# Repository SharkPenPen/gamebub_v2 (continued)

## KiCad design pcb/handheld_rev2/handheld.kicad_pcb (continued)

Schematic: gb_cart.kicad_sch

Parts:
C1901, C1902, C1903, C1904, C1905, C1906, C1907, C1908, C1909, C1910, C1911, C1912, C1913: 100n; C_0402_1005Metric; LCSC C1525
J1901: Cartridge_Slot; GameBoy_Cartridge_AGS_1x32-1MP_P1.50mm_Socket_Horizontal
R1901, R1902, R1905: 49R9; R_0402_1005Metric; LCSC C25120
R1903: 100K; R_0402_1005Metric; LCSC C25741
R1904: 27K; R_0603_1608Metric; LCSC C22967
U1901, U1903: 74LVC1T45; SOT-363_SC-70-6; LCSC C168855
U1902, U1904: 74LVCH16T245; TSSOP-48_6.1x12.5mm_P0.5mm; LCSC C352975

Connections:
+3V3_FPGA: C1903.2, C1904.2, C1906.2, C1909.2, C1912.2, C1913.2, R1903.1, U1901.1 (VCCA), U1902.31 (VCCA), U1902.42 (VCCA), U1903.1 (VCCA), U1904.31 (VCCA), U1904.42 (VCCA); also elsewhere on the board
/Game Boy Interfaces/Game Boy Cartridge/Cart_A16: J1901.22 (A16/D0), U1902.12 (1B8)
/Game Boy Interfaces/Game Boy Cartridge/Cart_A17: J1901.23 (A17/D1), U1902.11 (1B7)
/Game Boy Interfaces/Game Boy Cartridge/Cart_A18: J1901.24 (A18/D2), U1902.9 (1B6)
/Game Boy Interfaces/Game Boy Cartridge/Cart_A19: J1901.25 (A19/D3), U1902.8 (1B5)
/Game Boy Interfaces/Game Boy Cartridge/Cart_A20: J1901.26 (A20/D4), U1902.6 (1B4)
/Game Boy Interfaces/Game Boy Cartridge/Cart_A21: J1901.27 (A21/D5), U1902.5 (1B3)
/Game Boy Interfaces/Game Boy Cartridge/Cart_A22: J1901.28 (A22/D6), U1902.3 (1B2)
/Game Boy Interfaces/Game Boy Cartridge/Cart_A23: J1901.29 (A23/D7), U1902.2 (1B1)
/Game Boy Interfaces/Game Boy Cartridge/Cart_AD0: J1901.6 (AD0/A0), U1904.12 (1B8)
/Game Boy Interfaces/Game Boy Cartridge/Cart_AD1: J1901.7 (AD1/A1), U1904.11 (1B7)
/Game Boy Interfaces/Game Boy Cartridge/Cart_AD2: J1901.8 (AD2/A2), U1904.9 (1B6)
/Game Boy Interfaces/Game Boy Cartridge/Cart_AD3: J1901.9 (AD3/A3), U1904.8 (1B5)
/Game Boy Interfaces/Game Boy Cartridge/Cart_AD4: J1901.10 (AD4/A4), U1904.6 (1B4)
/Game Boy Interfaces/Game Boy Cartridge/Cart_AD5: J1901.11 (AD5/A5), U1904.5 (1B3)
/Game Boy Interfaces/Game Boy Cartridge/Cart_AD6: J1901.12 (AD6/A6), U1904.3 (1B2)
/Game Boy Interfaces/Game Boy Cartridge/Cart_AD7: J1901.13 (AD7/A7), U1904.2 (1B1)
/Game Boy Interfaces/Game Boy Cartridge/Cart_AD8: J1901.14 (AD8/A8), U1902.23 (2B8)
/Game Boy Interfaces/Game Boy Cartridge/Cart_AD9: J1901.15 (AD9/A9), U1902.22 (2B7)
/Game Boy Interfaces/Game Boy Cartridge/Cart_AD10: J1901.16 (AD10/A10), U1902.20 (2B6)
/Game Boy Interfaces/Game Boy Cartridge/Cart_AD11: J1901.17 (AD11/A11), U1902.19 (2B5)
/Game Boy Interfaces/Game Boy Cartridge/Cart_AD12: J1901.18 (AD12/A12), U1902.17 (2B4)
/Game Boy Interfaces/Game Boy Cartridge/Cart_AD13: J1901.19 (AD13/A13), U1902.16 (2B3)
/Game Boy Interfaces/Game Boy Cartridge/Cart_AD14: J1901.20 (AD14/A14), U1902.14 (2B2)
/Game Boy Interfaces/Game Boy Cartridge/Cart_AD15: J1901.21 (AD15/A15), U1902.13 (2B1)
/Game Boy Interfaces/Game Boy Cartridge/Cart_PHI: J1901.2 (PHI), U1904.17 (2B4)
/Game Boy Interfaces/Game Boy Cartridge/Cart_VIN: J1901.31 (~REQ/VIN), R1903.2, U1903.4 (B)
/Game Boy Interfaces/Game Boy Cartridge/Cart_~CS1: R1902.1, U1904.13 (2B1)
/Game Boy Interfaces/Game Boy Cartridge/Cart_~CS1_d: J1901.5 (~CS1/~CS), R1902.2
/Game Boy Interfaces/Game Boy Cartridge/Cart_~CS2: R1905.2, U1901.4 (B)
/Game Boy Interfaces/Game Boy Cartridge/Cart_~CS2_d: J1901.30 (~CS2/~RES), R1904.2, R1905.1
/Game Boy Interfaces/Game Boy Cartridge/Cart_~RD: J1901.4 (~RD), U1904.14 (2B2)
/Game Boy Interfaces/Game Boy Cartridge/Cart_~WR: R1901.2, U1904.16 (2B3)
/Game Boy Interfaces/Game Boy Cartridge/Cart_~WR_d: J1901.3 (~WR), R1901.1
GB_Cart_A16: U1902.37 (1A8); also elsewhere on the board
GB_Cart_A17: U1902.38 (1A7); also elsewhere on the board
GB_Cart_A18: U1902.40 (1A6); also elsewhere on the board
GB_Cart_A19: U1902.41 (1A5); also elsewhere on the board
GB_Cart_A20: U1902.43 (1A4); also elsewhere on the board
GB_Cart_A21: U1902.44 (1A3); also elsewhere on the board
GB_Cart_A22: U1902.46 (1A2); also elsewhere on the board
GB_Cart_A23: U1902.47 (1A1); also elsewhere on the board
GB_Cart_AD0: U1904.37 (1A8); also elsewhere on the board
GB_Cart_AD1: U1904.38 (1A7); also elsewhere on the board
GB_Cart_AD2: U1904.40 (1A6); also elsewhere on the board
GB_Cart_AD3: U1904.41 (1A5); also elsewhere on the board
GB_Cart_AD4: U1904.43 (1A4); also elsewhere on the board
GB_Cart_AD5: U1904.44 (1A3); also elsewhere on the board
GB_Cart_AD6: U1904.46 (1A2); also elsewhere on the board
GB_Cart_AD7: U1904.47 (1A1); also elsewhere on the board
GB_Cart_AD8: U1902.26 (2A8); also elsewhere on the board
GB_Cart_AD9: U1902.27 (2A7); also elsewhere on the board
GB_Cart_AD10: U1902.29 (2A6); also elsewhere on the board
GB_Cart_AD11: U1902.30 (2A5); also elsewhere on the board
GB_Cart_AD12: U1902.32 (2A4); also elsewhere on the board
GB_Cart_AD13: U1902.33 (2A3); also elsewhere on the board
GB_Cart_AD14: U1902.35 (2A2); also elsewhere on the board
GB_Cart_AD15: U1902.36 (2A1); also elsewhere on the board
GB_Cart_PHI: U1904.32 (2A4); also elsewhere on the board
GB_Cart_VIN: U1903.3 (A); also elsewhere on the board
GB_Cart_~CS1: U1904.36 (2A1); also elsewhere on the board
GB_Cart_~CS2: U1901.3 (A); also elsewhere on the board
GB_Cart_~OE: U1902.25 (2~OE), U1902.48 (1~OE), U1904.25 (2~OE), U1904.48 (1~OE); also elsewhere on the board
GB_Cart_~RD: U1904.35 (2A2); also elsewhere on the board
GB_Cart_~WR: U1904.33 (2A3); also elsewhere on the board
GB_Dir_Cart0: U1902.1 (1DIR); also elsewhere on the board
GB_Dir_Cart1: U1902.24 (2DIR); also elsewhere on the board
GB_Dir_Cart2: U1904.1 (1DIR); also elsewhere on the board
GB_Dir_Cart3: U1904.24 (2DIR); also elsewhere on the board
GB_Dir_VIN: U1903.5 (DIR); also elsewhere on the board
GB_Dir_~CS2: U1901.5 (DIR); also elsewhere on the board
GND: C1901.1, C1902.1, C1903.1, C1904.1, C1905.1, C1906.1, C1907.1, C1908.1, C1909.1, C1910.1, C1911.1, C1912.1, C1913.1, J1901.32 (GND), J1901.MP, U1901.2 (GND), U1902.4 (GND), U1902.10 (GND), U1902.15 (GND), U1902.21 (GND), U1902.28 (GND), U1902.34 (GND), U1902.39 (GND), U1902.45 (GND), U1903.2 (GND), U1904.4 (GND), U1904.10 (GND), U1904.15 (GND), U1904.19 (2B5), U1904.20 (2B6), U1904.21 (GND), U1904.22 (2B7), U1904.23 (2B8), U1904.26 (2A8), U1904.27 (2A7), U1904.28 (GND), U1904.29 (2A6), U1904.30 (2A5), U1904.34 (GND), U1904.39 (GND), U1904.45 (GND); also elsewhere on the board
VGB: C1901.2, C1902.2, C1905.2, C1907.2, C1908.2, C1910.2, C1911.2, J1901.1 (VDD), R1904.1, U1901.6 (VCCB), U1902.7 (VCCB), U1902.18 (VCCB), U1903.6 (VCCB), U1904.7 (VCCB), U1904.18 (VCCB); also elsewhere on the board

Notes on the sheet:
AGS uses 18K for CS2 pull-up
AGS uses 47Ω for WR/CS1 resistor
AGS uses 15Ω for CS2 limiter

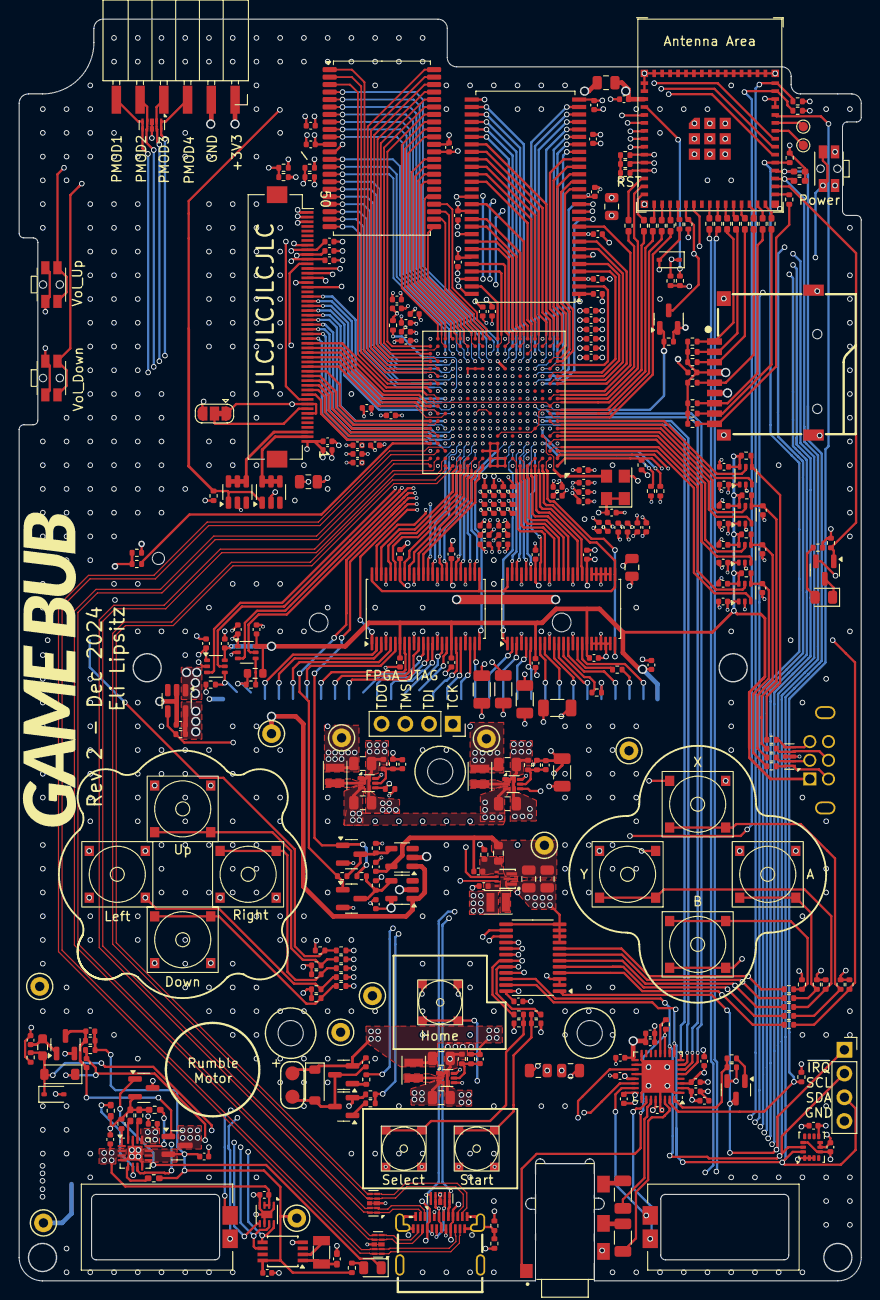
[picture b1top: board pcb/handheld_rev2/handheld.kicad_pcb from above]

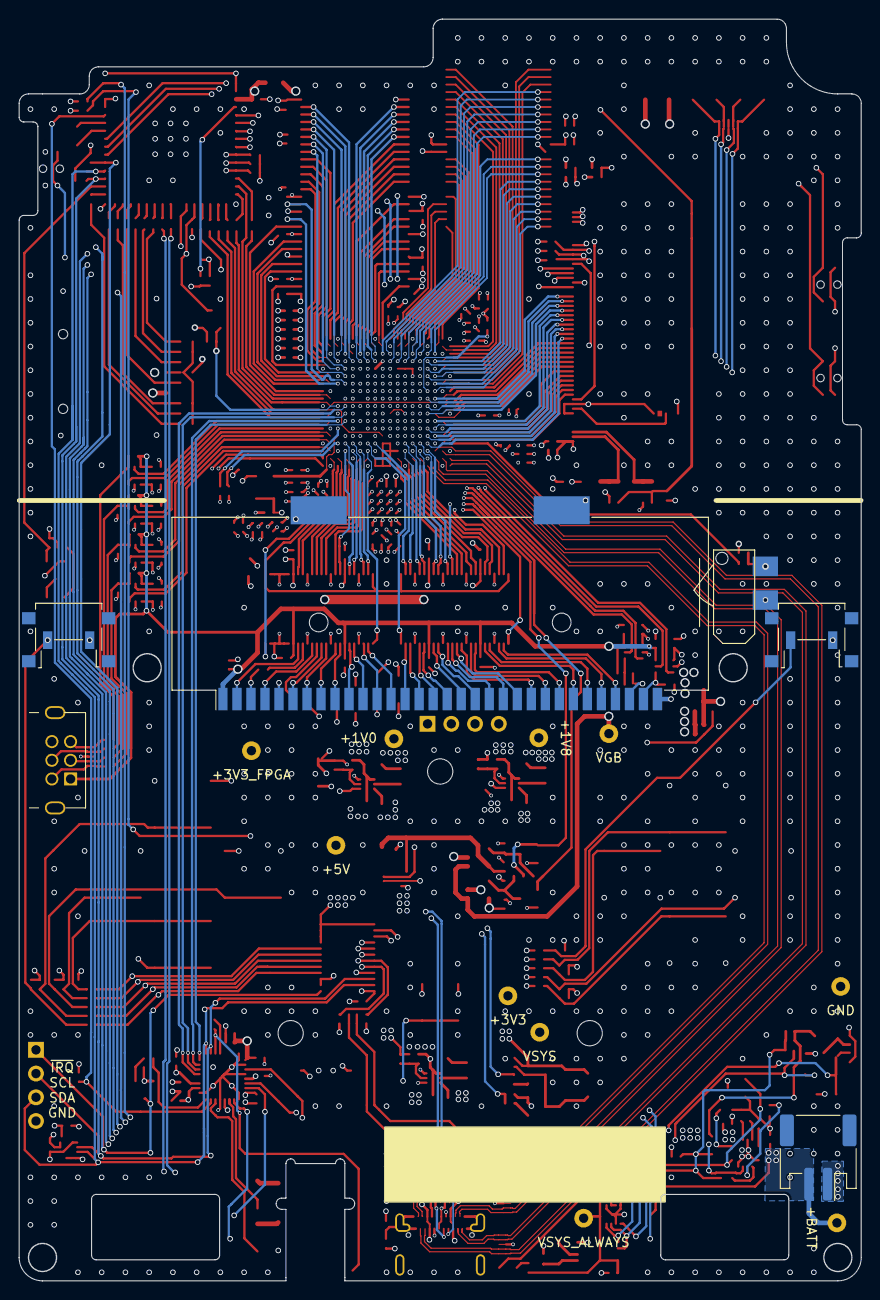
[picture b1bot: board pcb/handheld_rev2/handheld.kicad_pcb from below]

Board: 6 copper layers, 90.1 x 135.0 mm, 359 parts (6 on the bottom side), 360 nets.

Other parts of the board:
C2001, C2002, C2003: 100p; C_0402_1005Metric
R2001, R2002, R2003, R2004: 330R; R_0402_1005Metric

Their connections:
/Game Boy Interfaces/Game Boy Link/Link_SC: R2004.2; also elsewhere on the board
/Game Boy Interfaces/Game Boy Link/Link_SC_a: R2004.1; also elsewhere on the board
/Game Boy Interfaces/Game Boy Link/Link_SD: C2001.1, R2003.2; also elsewhere on the board
/Game Boy Interfaces/Game Boy Link/Link_SD_a: R2003.1; also elsewhere on the board
/Game Boy Interfaces/Game Boy Link/Link_SI: C2002.1, R2002.2; also elsewhere on the board
/Game Boy Interfaces/Game Boy Link/Link_SI_a: R2002.1; also elsewhere on the board
/Game Boy Interfaces/Game Boy Link/Link_SO: C2003.1, R2001.2; also elsewhere on the board
/Game Boy Interfaces/Game Boy Link/Link_SO_a: R2001.1; also elsewhere on the board
GND: C2001.2, C2002.2, C2003.2; also elsewhere on the board
